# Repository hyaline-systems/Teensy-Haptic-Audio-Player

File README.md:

# Teensy-Haptic-Audio-Player

A PCB designed for audio and haptic projects with [a Teensy 4.0](https://www.pjrc.com/store/teensy40.html). 

Among other things, it can be used to play audio from the computer as a sound card when connected via USB or from audio files via the on board SD card reader. The audio will then be output both to a 3.5mm audio jack and a haptic driver that will make a vibration motor [like this one](https://www.adafruit.com/product/1201) vibrate in sync with the audio, kinda like in a gamepad, sex toy or phone.

Another usecase is simply as a high quality audio development platform.

The whole thing is open source and hackable and is designed to be used for many different scenarios.

See [hyaline.systems](https://hyaline.systems) for more information. 

## Buying

You can buy a board, either bare (no components) or SMD-populated (no Teensy included) by sending an email to [hi@hyaline.systems](mailto:hi@hyalyne.systems).

If you just want to support the project, [consider making a donation through kofi](https://ko-fi.com/madskjeldgaard).

## Features

- Designed for the very powerful Teensy 4.0 board.
- High quality i2s stereo output DAC with 3.5mm line out jack: [PCM5102A DAC](https://www.ti.com/product/PCM5102A) – this DAC is widely compatible with all platforms and SDK's, including Arduino and C.
- SD card reader
- NeoPixel
- StemmaQT connector for easy i2c expansion.
- Optional: Hardware mute button may be connected directly to DAC.
- All unused pins broken out with lots of ground and power pins to make external connections easy
- Self-documenting board: All pins and connections are written on the board itself.

## Software

See [software/examples](software/examples) for example code using Arduino.

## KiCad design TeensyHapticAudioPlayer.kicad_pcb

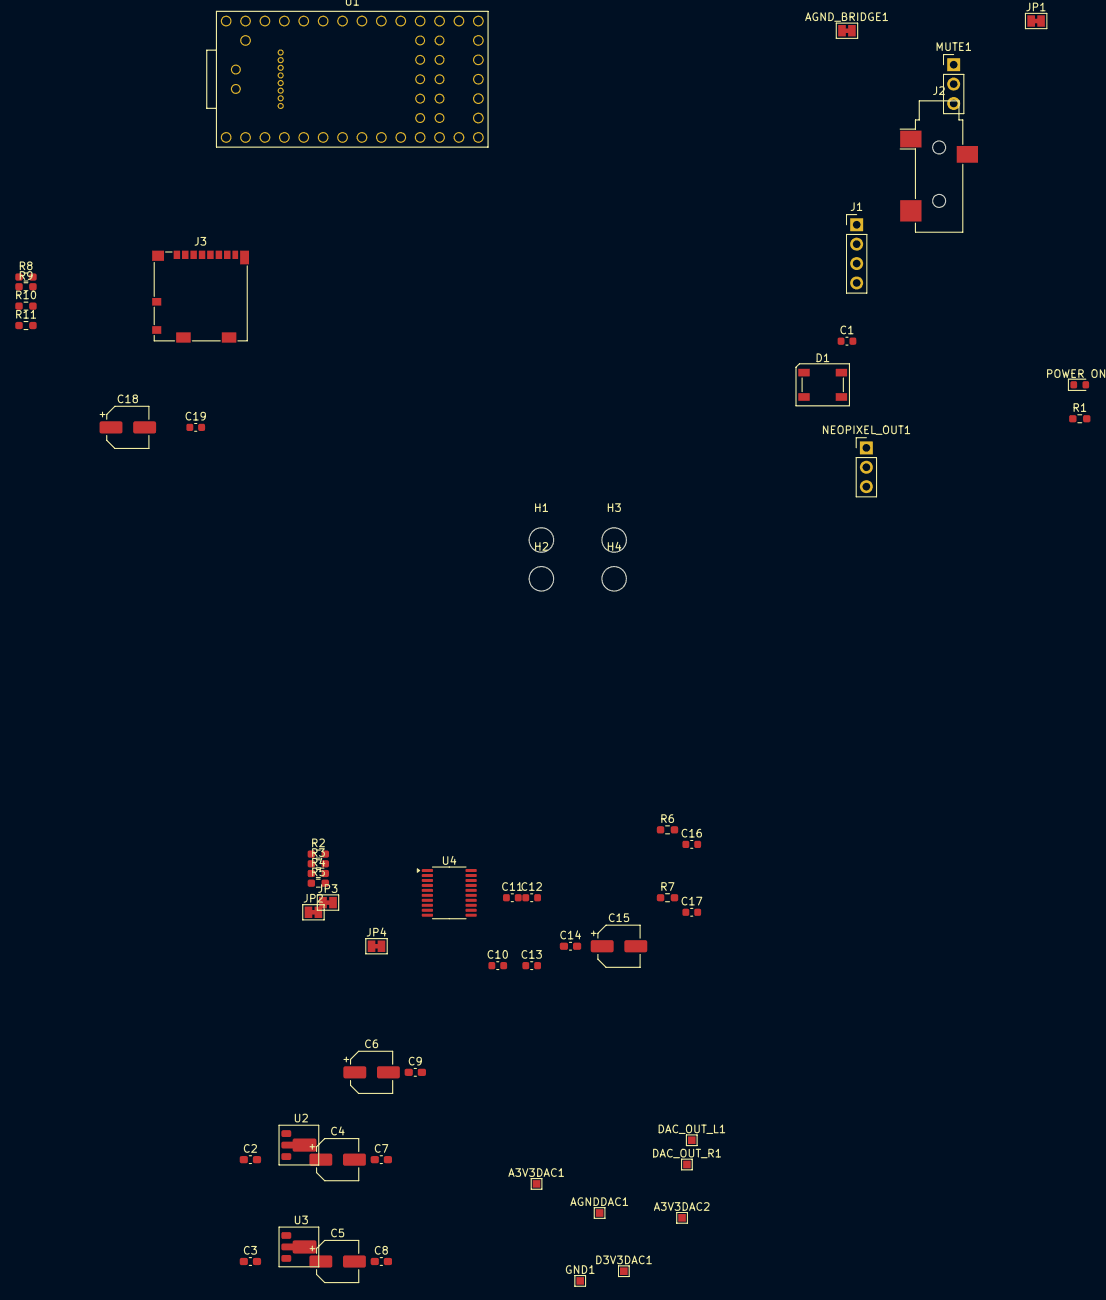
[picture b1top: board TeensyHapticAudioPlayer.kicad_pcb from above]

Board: 2 copper layers, 57 parts (0 on the bottom side), 31 nets, no tracks yet.

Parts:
A3V3DAC1, A3V3DAC2: TP; TestPoint_Pad_1.0x1.0mm
AGNDDAC1: TP; TestPoint_Pad_1.0x1.0mm
AGND_BRIDGE1: AGND_BRIDGE; SolderJumper-2_P1.3mm_Bridged_Pad1.0x1.5mm
C1, C10, C11, C12, C13: 1uf; C_0603_1608Metric
C2, C3, C7, C8, C9, C14: 0.1uf; C_0603_1608Metric_Pad1.08x0.95mm_HandSolder
C4, C5, C6, C15, C18: 10uf; CP_Elec_5x5.7
C16, C17: 1nf; C_0603_1608Metric
C19: 0.1uf; C_0603_1608Metric
D1: SK6812; LED_SK6812_PLCC4_5.0x5.0mm_P3.2mm
D3V3DAC1: TP; TestPoint_Pad_1.0x1.0mm
DAC_OUT_L1: TP; TestPoint_Pad_1.0x1.0mm
DAC_OUT_R1: TP; TestPoint_Pad_1.0x1.0mm
GND1: TP; TestPoint_Pad_1.0x1.0mm
H1, H2, H3, H4: MountingHole; MountingHole_3.2mm_M3
J1: Conn_01x04; PinHeader_1x04_P2.54mm_Vertical
J2: AudioJack3; Jack_3.5mm_CUI_SJ-3523-SMT_Horizontal
J3: Micro_SD_Card; microSD_HC_Molex_104031-0811
JP1: MUTE_BRIDGE; SolderJumper-2_P1.3mm_Bridged_Pad1.0x1.5mm
JP2, JP3, JP4: SolderJumper_2_Bridged; SolderJumper-2_P1.3mm_Bridged_Pad1.0x1.5mm
MUTE1: Conn_01x03; PinHeader_1x03_P2.54mm_Vertical
NEOPIXEL_OUT1: Conn_01x03; PinHeader_1x03_P2.54mm_Vertical
POWER ON1: LED; LED_0603_1608Metric
R1: 10K; R_0603_1608Metric_Pad0.98x0.95mm_HandSolder
R2, R3, R4, R5: 22; R_0603_1608Metric_Pad0.98x0.95mm_HandSolder
R6, R7: 470; R_0603_1608Metric_Pad0.98x0.95mm_HandSolder
R8, R9, R10, R11: 47k; R_0603_1608Metric_Pad0.98x0.95mm_HandSolder
U1: Teensy4.0; Teensy40_SMT
U2, U3: AP7365-33YG; SOT-89-3
U4: PCM5102A; TSSOP-20_4.4x6.5mm_P0.65mm

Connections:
+3.3V: C1.1, C18.1, C19.1, D1.3 (VDD), J3.4 (VDD), JP1.2 (B), MUTE1.3, NEOPIXEL_OUT1.2, R1.1, R8.1, R9.1, R10.1, R11.1
+5V: C2.1, C3.1, U2.3 (IN), U3.3 (IN)
/AGND: AGNDDAC1.1, AGND_BRIDGE1.1 (A), C4.2, C6.2, C7.2, C9.2, C10.2, C13.2, C16.2, C17.2, J1.2, J1.4, J2.S, U4.3 (CPGND), U4.9 (AGND)
/DAC_BCK: R4.1, U1.28 (21_A7_RX5_BCLK1)
/DAC_DIN: R3.1, U1.9 (7_RX2_OUT1A)
/DAC_LRCK: R2.1, U1.27 (20_A6_TX5_LRCLK1)
/DAC_MUTE: JP1.1 (A), MUTE1.2, U4.17 (XSMT)
/DAC_OUT_L: C16.1, DAC_OUT_L1.1, J1.1, J2.T, R6.1
/DAC_OUT_R: C17.1, DAC_OUT_R1.1, J1.3, J2.R, R7.1
/NEOPIXEL_OUT: D1.4 (DOUT), NEOPIXEL_OUT1.1
/PCM5102A DAC/3V3A: A3V3DAC1.1, A3V3DAC2.1, C4.1, C6.1, C7.1, C9.1, U2.1 (OUT), U4.1 (CPVDD), U4.8 (AVDD)
/PCM5102A DAC/3V3D: C5.1, C8.1, D3V3DAC1.1, U3.1 (OUT), U4.20 (DVDD)
/SD_CS: J3.2 (DAT3/CD), R8.2
/SD_MISO: J3.7 (DAT0), R11.2
/SD_MOSI: J3.3 (CMD), R9.2
/SD_SCK: J3.5 (CLK), R10.2
GND: AGND_BRIDGE1.2 (B), C1.2, C2.2, C3.2, C5.2, C8.2, C14.2, C15.2, C18.2, C19.2, D1.1 (VSS), GND1.1, J3.6 (VSS), J3.9 (SHIELD), JP2.1 (A), JP3.1 (A), JP4.1 (A), MUTE1.1, NEOPIXEL_OUT1.3, POWER ON1.1 (K), R5.1, U2.2, U3.2, U4.19 (DGND)
unnamed: JP2.2 (B), U4.10 (DEMP)
unnamed: JP3.2 (B), U4.11 (FLT)
unnamed: JP4.2 (B), U4.16 (FMT)
unnamed: POWER ON1.2 (A), R1.2
unnamed: R4.2, U4.13 (BCK)
unnamed: C11.2, C12.2, U4.4 (CAPM)
unnamed: C11.1, C12.1, U4.2 (CAPP)
unnamed: R3.2, U4.14 (DIN)
unnamed: C14.1, C15.1, U4.18 (LDOO)
unnamed: R2.2, U4.15 (LRCK)
unnamed: R6.2, U4.6 (OUTL)
unnamed: R7.2, U4.7 (OUTR)
unnamed: R5.2, U4.12 (SCK)
unnamed: C10.1, C13.1, U4.5 (VNEG)

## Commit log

2025-01-23 first
2025-01-23 update reamde
2025-01-31 reorganize
2025-01-31 finish usb interface example
2025-02-01 docs: haptic audio interface example done
2025-02-01 finish wav player example
2025-02-03 fix readme
2025-02-03 info about
2025-02-03 donation
2025-02-17 fix: Set brightness to something less bonkers

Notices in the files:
README.md:
License: CC BY-NC-SA 4.0
